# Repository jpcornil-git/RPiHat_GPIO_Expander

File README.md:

# RPiHat_GPIO_Expander
Main motivation behind this design was to design an input/output system for home automation able to control 230VAC equipments without exposing hazardous voltages (as it is usually the case with popular relay expansion boards) as well as support high current requirements. DIN-rail mount relays meet both requirements and can be controlled using a 24V DC voltage and reasonable current levels. The same 24V voltage can also be used for input devices (buttons, switches …) while offering high noise immunity.  

This Raspberry HAT design allows to control up to 8x DIN-rail mount relays (24VDC, ~25mA coil current) and sense up to 8x 24VDC inputs. It also integrates a 24V->5V DCDC converter that may be used to power the Raspberry motherboard and avoid the need for an additional USB adapter and associated wall plug in the distribution panel. 

This repository includes all design informations (eagle schematic/layout, Gerber, BOM, ...) and related documentation

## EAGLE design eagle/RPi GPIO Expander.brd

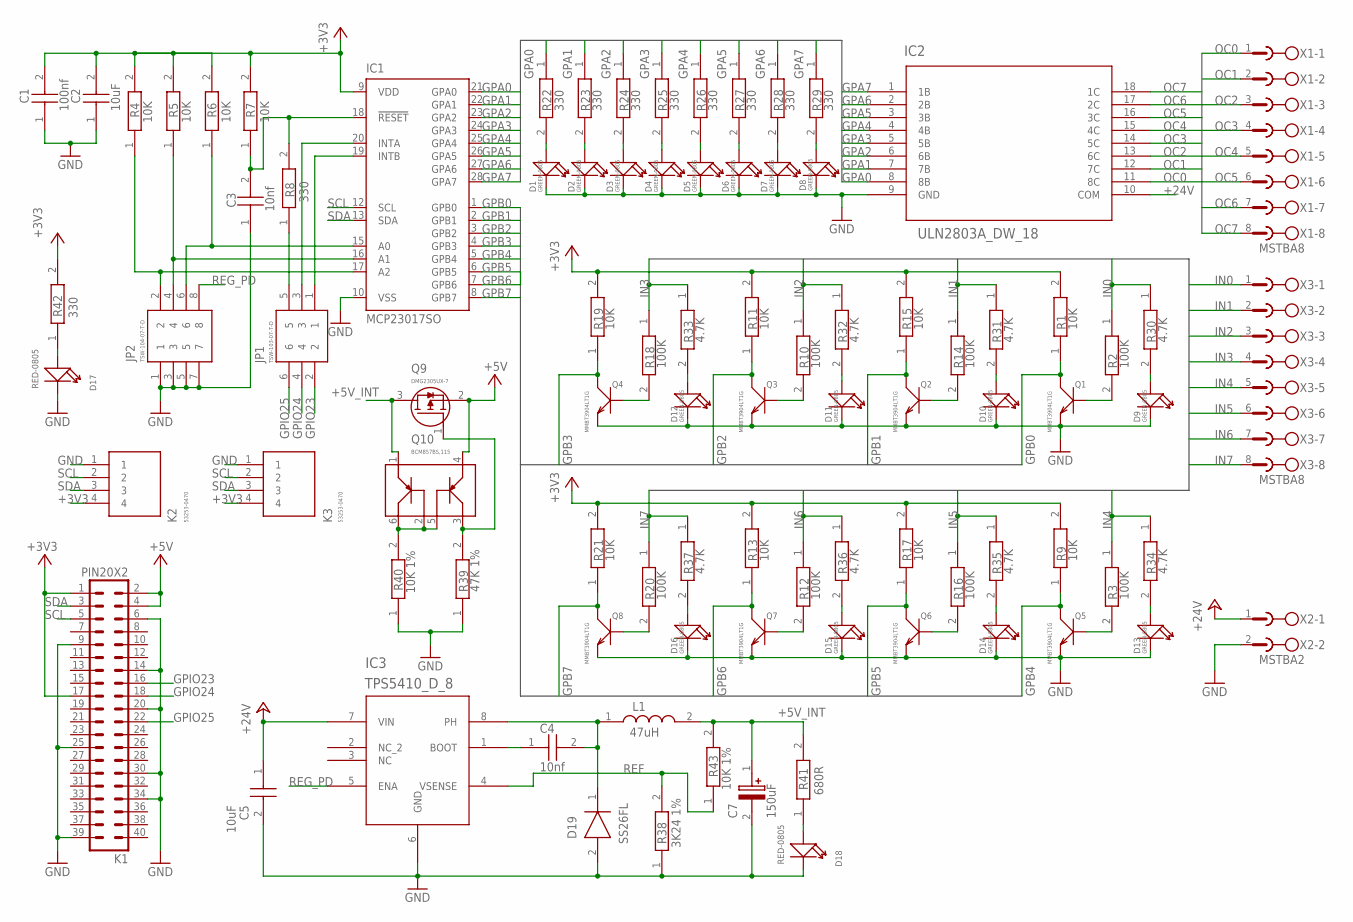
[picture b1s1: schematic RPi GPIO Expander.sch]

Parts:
C1: 100nf; CAPC2012X95N
C2: 10uF; CAPC2013X145N
C3, C4: 10nf; CAPC2012X135N
C5: 10uF; CAPC3225X230N
C7: 150uF; CAPPM3629X150N
D1, D2, D3, D4, D5, D6, D7, D8, D9, D10, D11, D12, D13, D14, D15, D16: GREEN-0805; LED-0805
D17, D18: RED-0805; LED-0805
D19: SS26FL; SODFL3617X108N
IC1: MCP23017SO; SO28W
IC2: ULN2803A_DW_18; DW18
IC3: TPS5410_D_8; D8
JP1: TSW-103-07-T-D; HDRV6W64P254_2X3_762X495X838P
JP2: TSW-104-07-T-D; HDRV8W64P254_2X4_1016X495X838P
K1: PIN20X2; PIN_20X2
K2, K3: 53253-0470; SHDR4W50P0X200_1X4_1000X365X55
L1: 47uH; INDPM101100X630N
Q1, Q2, Q3, Q4, Q5, Q6, Q7, Q8: MMBT3904LT1G; SOT-23
Q9: DMG2305UX-7; SOT96P240X100-3N
Q10: BCM857BS,115; SOT65P210X110-6N
R1, R4, R5, R6, R7, R9, R11, R13, R15, R17, R19, R21: 10K; RESC2012X60N
R2, R3, R10, R12, R14, R16, R18, R20: 100K; RESC2012X60N
R8, R22, R23, R24, R25, R26, R27, R28, R29, R42: 330; RESC2012X60N
R30, R31, R32, R33, R34, R35, R36, R37: 4.7K; RESC2012X60N
R38: 3K24 1%; RESC2012X60N
R39: 47K 1%; RESC2012X60N
R40, R43: 10K 1%; RESC2012X60N
R41: 680R; RESC2012X60N
X1, X3: MSTBA8
X2: MSTBA2

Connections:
+3V3: C1.2, C2.2 (C2), IC1.9 (VDD), K1.1, K1.17, K2.4, K3.4, R1.2, R4.2, R5.2, R6.2, R7.2, R9.2, R11.2, R13.2, R15.2, R17.2, R19.2, R21.2, R42.2
+5V: K1.2, K1.4, Q9.2 (S), Q10.4
+5V_INT: C7.1 (+), L1.2, Q9.3 (D), Q10.1, R41.2, R43.2
+24V: C5.1, IC2.10 (COM), IC3.7 (VIN), X2.1
GND: C1.1, C2.1 (C1), C3.1, C5.2, C7.2 (-), D1.-, D2.-, D3.-, D4.-, D5.-, D6.-, D7.-, D8.-, D9.-, D10.-, D11.-, D12.-, D13.-, D14.-, D15.-, D16.-, D17.-, D18.-, D19.2 (A), IC1.10 (VSS), IC2.9 (GND), IC3.6 (GND), JP2.1, JP2.3, JP2.5, JP2.7, K1.6, K1.9, K1.14, K1.20, K1.25, K1.30, K1.34, K1.39, K2.1, K3.1, Q1.2 (E), Q2.2 (E), Q3.2 (E), Q4.2 (E), Q5.2 (E), Q6.2 (E), Q7.2 (E), Q8.2 (E), R38.1, R39.1, R40.1, X2.2
GPA0: IC1.21 (GPA0), IC2.8 (8B), R22.1
GPA1: IC1.22 (GPA1), IC2.7 (7B), R23.1
GPA2: IC1.23 (GPA2), IC2.6 (6B), R24.1
GPA3: IC1.24 (GPA3), IC2.5 (5B), R25.1
GPA4: IC1.25 (GPA4), IC2.4 (4B), R26.1
GPA5: IC1.26 (GPA5), IC2.3 (3B), R27.1
GPA6: IC1.27 (GPA6), IC2.2 (2B), R28.1
GPA7: IC1.28 (GPA7), IC2.1 (1B), R29.1
GPB0: IC1.1 (GPB0), Q1.3 (C), R1.1
GPB1: IC1.2 (GPB1), Q2.3 (C), R15.1
GPB2: IC1.3 (GPB2), Q3.3 (C), R11.1
GPB3: IC1.4 (GPB3), Q4.3 (C), R19.1
GPB4: IC1.5 (GPB4), Q5.3 (C), R9.1
GPB5: IC1.6 (GPB5), Q6.3 (C), R17.1
GPB6: IC1.7 (GPB6), Q7.3 (C), R13.1
GPB7: IC1.8 (GPB7), Q8.3 (C), R21.1
GPIO23: JP1.2, K1.16
GPIO24: JP1.4, K1.18
GPIO25: JP1.6, K1.22
IN0: R2.1, R30.1, X3.1
IN1: R14.1, R31.1, X3.2
IN2: R10.1, R32.1, X3.3
IN3: R18.1, R33.1, X3.4
IN4: R3.1, R34.1, X3.5
IN5: R16.1, R35.1, X3.6
IN6: R12.1, R36.1, X3.7
IN7: R20.1, R37.1, X3.8
unnamed: D12.+, R33.2
unnamed: D1.+, R22.2
unnamed: Q1.1 (B), R2.2
unnamed: IC1.19 (INTB), JP1.1
unnamed: JP1.5, R8.1
unnamed: D2.+, R23.2
unnamed: D3.+, R24.2
unnamed: D4.+, R25.2
unnamed: D5.+, R26.2
unnamed: D6.+, R27.2
unnamed: D7.+, R28.2
unnamed: IC1.15 (A0), JP2.6, R6.1
unnamed: IC1.16 (A1), JP2.4, R5.1
unnamed: IC1.17 (A2), JP2.2, R4.1
unnamed: C3.2, IC1.18 (!RESET), R7.1, R8.2
unnamed: IC1.20 (INTA), JP1.3
unnamed: D11.+, R32.2
unnamed: Q5.1 (B), R3.2
unnamed: D10.+, R31.2
unnamed: Q3.1 (B), R10.2
unnamed: D9.+, R30.2
unnamed: Q7.1 (B), R12.2
unnamed: D13.+, R34.2
unnamed: Q2.1 (B), R14.2
unnamed: D14.+, R35.2
unnamed: Q6.1 (B), R16.2
unnamed: D15.+, R36.2
unnamed: Q4.1 (B), R18.2
unnamed: D16.+, R37.2
unnamed: Q8.1 (B), R20.2
unnamed: D8.+, R29.2
unnamed: Q10.2, Q10.5, Q10.6, R40.2
unnamed: C4.2, D19.1 (K), IC3.8 (PH), L1.1
unnamed: D18.+, R41.1
unnamed: C4.1, IC3.1 (BOOT)
unnamed: D17.+, R42.1
unnamed: Q9.1 (G), Q10.3, R39.2
OC0: IC2.11 (8C), X1.1
OC1: IC2.12 (7C), X1.2
OC2: IC2.13 (6C), X1.3
OC3: IC2.14 (5C), X1.4
OC4: IC2.15 (4C), X1.5
OC5: IC2.16 (3C), X1.6
OC6: IC2.17 (2C), X1.7
OC7: IC2.18 (1C), X1.8
REF: IC3.4 (VSENSE), R38.2, R43.1
REG_PD: IC3.5 (ENA), JP2.8
SCL: IC1.12 (SCL), K1.5, K2.2, K3.2
SDA: IC1.13 (SDA), K1.3, K2.3, K3.3

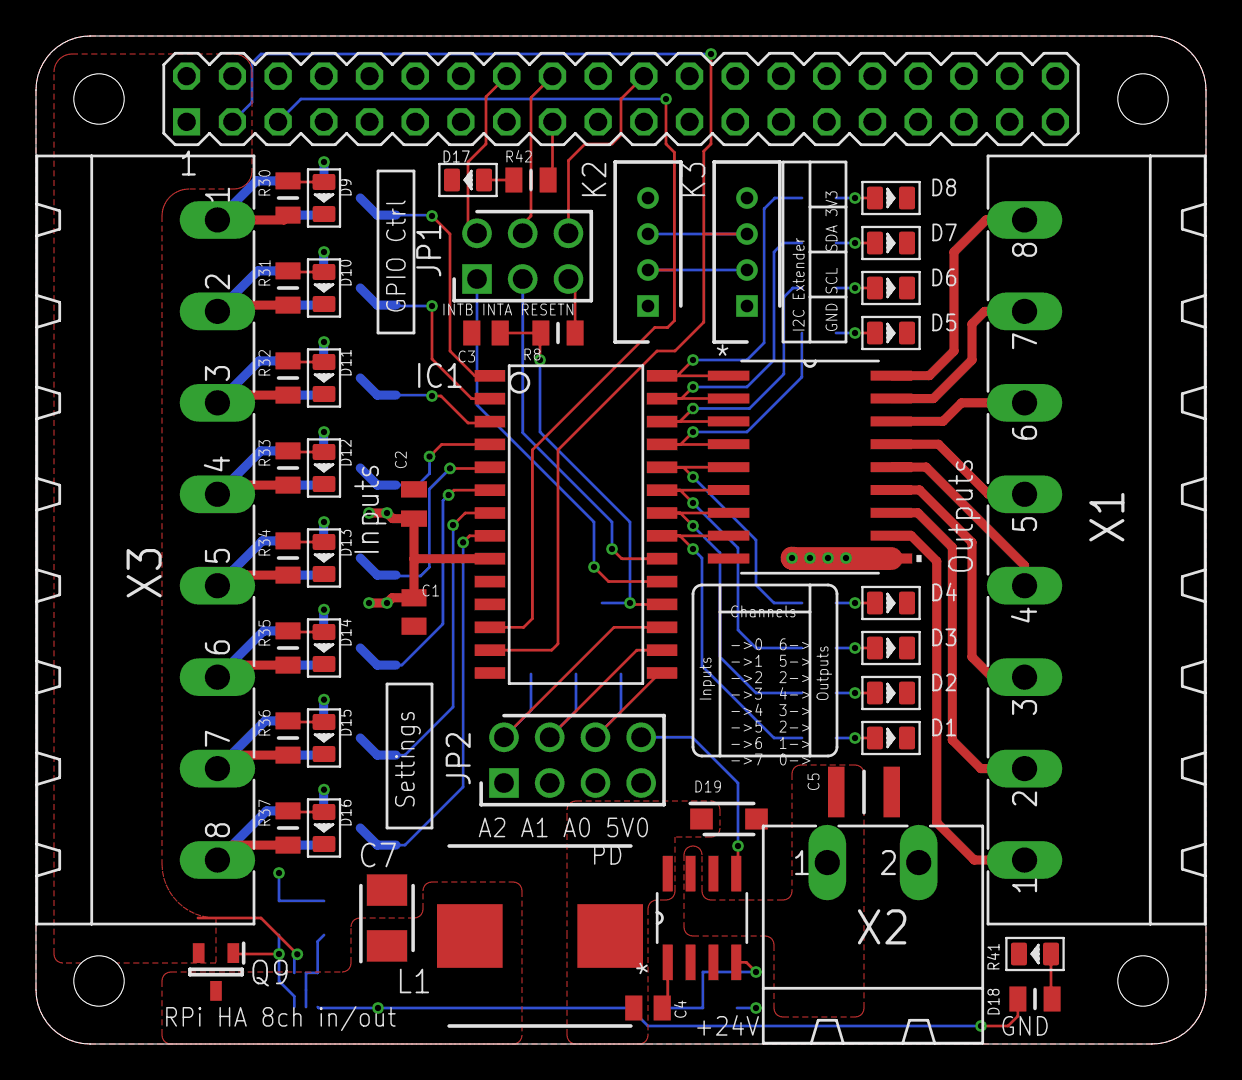
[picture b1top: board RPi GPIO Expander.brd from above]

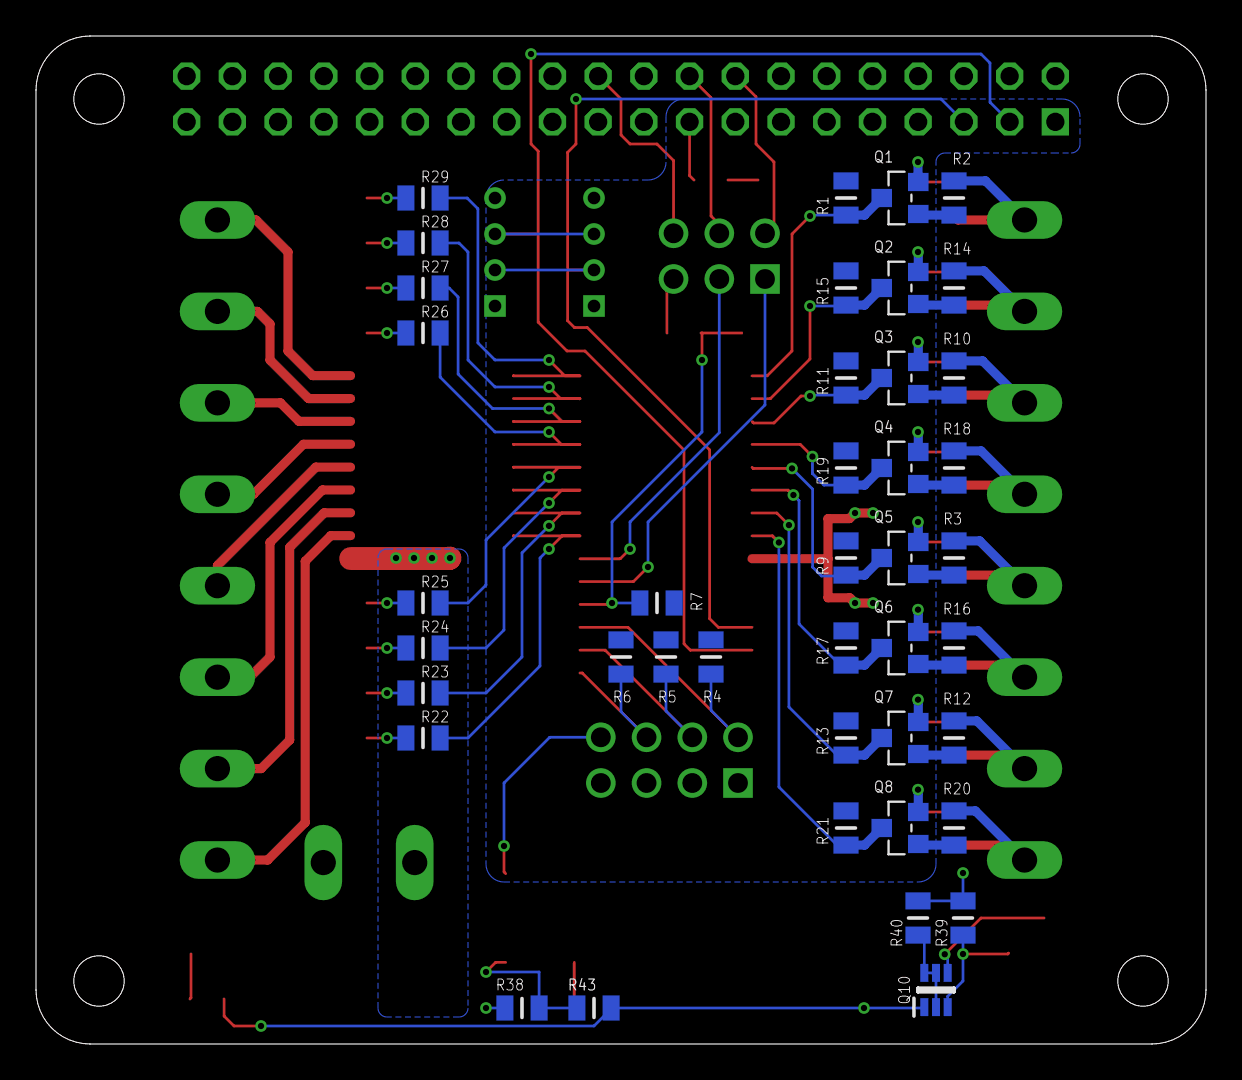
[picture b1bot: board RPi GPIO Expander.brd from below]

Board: 2 copper layers, 65.0 x 56.0 mm, 90 parts (41 on the bottom side), 81 nets.

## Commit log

2020-02-16 Initial Checkin
